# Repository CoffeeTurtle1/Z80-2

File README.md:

# Z802
A Z80 based computer.

The current PCB revision is `Z802-6.kicad_pcb`.

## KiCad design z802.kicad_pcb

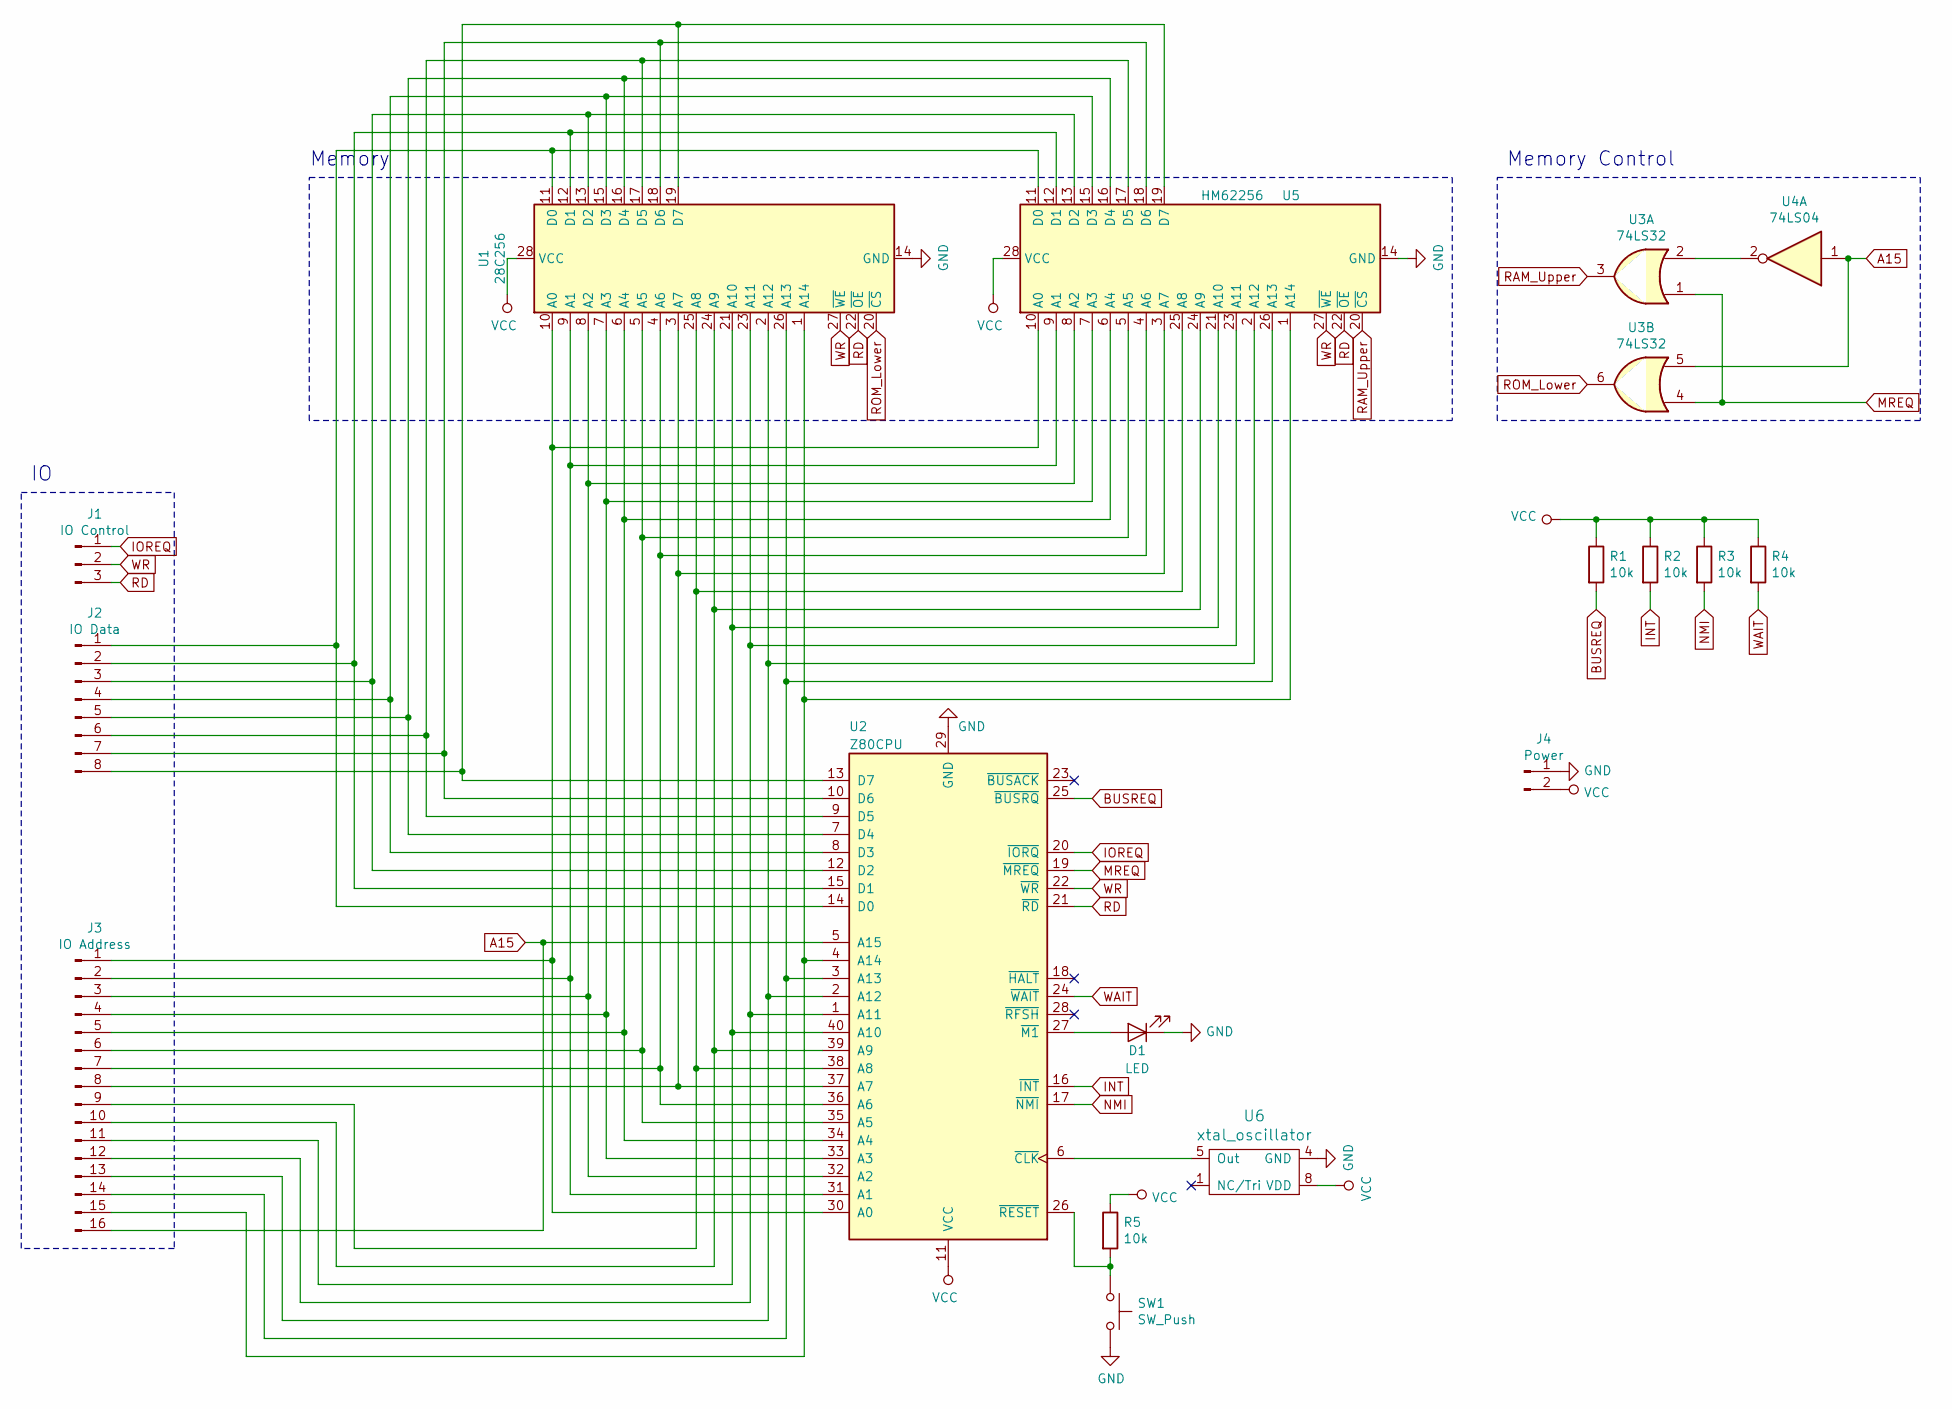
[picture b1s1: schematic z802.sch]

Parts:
D1: LED; LED_D3.0mm
J1: IO Control; PinHeader_1x03_P2.00mm_Vertical
J2: IO Data; PinHeader_1x08_P2.00mm_Vertical
J3: IO Address; PinHeader_1x16_P2.00mm_Vertical
J4: Power; PinHeader_1x02_P2.00mm_Vertical
R1, R2, R3, R4, R5: 10k; R_Axial_DIN0207_L6.3mm_D2.5mm_P7.62mm_Horizontal
SW1: SW_Push; SW_PUSH_6mm
U1: 28C256; DIP-28_W15.24mm
U2: Z80CPU; DIP-40_W15.24mm
U3: 74LS32; DIP-14_W7.62mm
U4: 74LS04; DIP-14_W7.62mm
U5: HM62256; DIP-28_W15.24mm
U6: xtal_oscillator; Oscillator_DIP-8

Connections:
A15: J3.16, U2.5 (A15), U3.5, U4.1
BUSREQ: R1.2, U2.25 (~BUSRQ~)
GND: D1.1 (K), J4.1, SW1.2, U1.14 (GND), U2.29 (GND), U5.14 (GND), U6.4 (GND)
INT: R2.2, U2.16 (~INT~)
IOREQ: J1.1, U2.20 (~IORQ~)
MREQ: U2.19 (~MREQ~), U3.1, U3.4
NMI: R3.2, U2.17 (~NMI~)
unnamed: D1.2 (A), U2.27 (~M1~)
unnamed: J2.1, U1.11 (D0), U2.14 (D0), U5.11 (D0)
unnamed: J2.2, U1.12 (D1), U2.15 (D1), U5.12 (D1)
unnamed: J2.3, U1.13 (D2), U2.12 (D2), U5.13 (D2)
unnamed: J2.4, U1.15 (D3), U2.8 (D3), U5.15 (D3)
unnamed: J2.5, U1.16 (D4), U2.7 (D4), U5.16 (D4)
unnamed: J2.6, U1.17 (D5), U2.9 (D5), U5.17 (D5)
unnamed: J2.7, U1.18 (D6), U2.10 (D6), U5.18 (D6)
unnamed: J2.8, U1.19 (D7), U2.13 (D7), U5.19 (D7)
unnamed: J3.1, U1.10 (A0), U2.30 (A0), U5.10 (A0)
unnamed: J3.2, U1.9 (A1), U2.31 (A1), U5.9 (A1)
unnamed: J3.3, U1.8 (A2), U2.32 (A2), U5.8 (A2)
unnamed: J3.4, U1.7 (A3), U2.33 (A3), U5.7 (A3)
unnamed: J3.5, U1.6 (A4), U2.34 (A4), U5.6 (A4)
unnamed: J3.6, U1.5 (A5), U2.35 (A5), U5.5 (A5)
unnamed: J3.7, U1.4 (A6), U2.36 (A6), U5.4 (A6)
unnamed: J3.8, U1.3 (A7), U2.37 (A7), U5.3 (A7)
unnamed: J3.9, U1.25 (A8), U2.38 (A8), U5.25 (A8)
unnamed: J3.10, U1.24 (A9), U2.39 (A9), U5.24 (A9)
unnamed: J3.11, U1.21 (A10), U2.40 (A10), U5.21 (A10)
unnamed: J3.12, U1.23 (A11), U2.1 (A11), U5.23 (A11)
unnamed: J3.13, U1.2 (A12), U2.2 (A12), U5.2 (A12)
unnamed: J3.14, U1.26 (A13), U2.3 (A13), U5.26 (A13)
unnamed: J3.15, U1.1 (A14), U2.4 (A14), U5.1 (A14)
unnamed: R5.2, SW1.1, U2.26 (~RESET~)
unnamed: U2.6 (~CLK~), U6.5 (Out)
unnamed: U3.2, U4.2
RAM_Upper: U3.3, U5.20 (~CS)
RD: J1.3, U1.22 (~OE), U2.21 (~RD~), U5.22 (~OE)
ROM_Lower: U1.20 (~CS), U3.6
VCC: J4.2, R1.1, R2.1, R3.1, R4.1, R5.1, U1.28 (VCC), U2.11 (VCC), U5.28 (VCC), U6.8 (VDD)
WAIT: R4.2, U2.24 (~WAIT~)
WR: J1.2, U1.27 (~WE), U2.22 (~WR~), U5.27 (~WE)

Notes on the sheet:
Memory Control
Memory

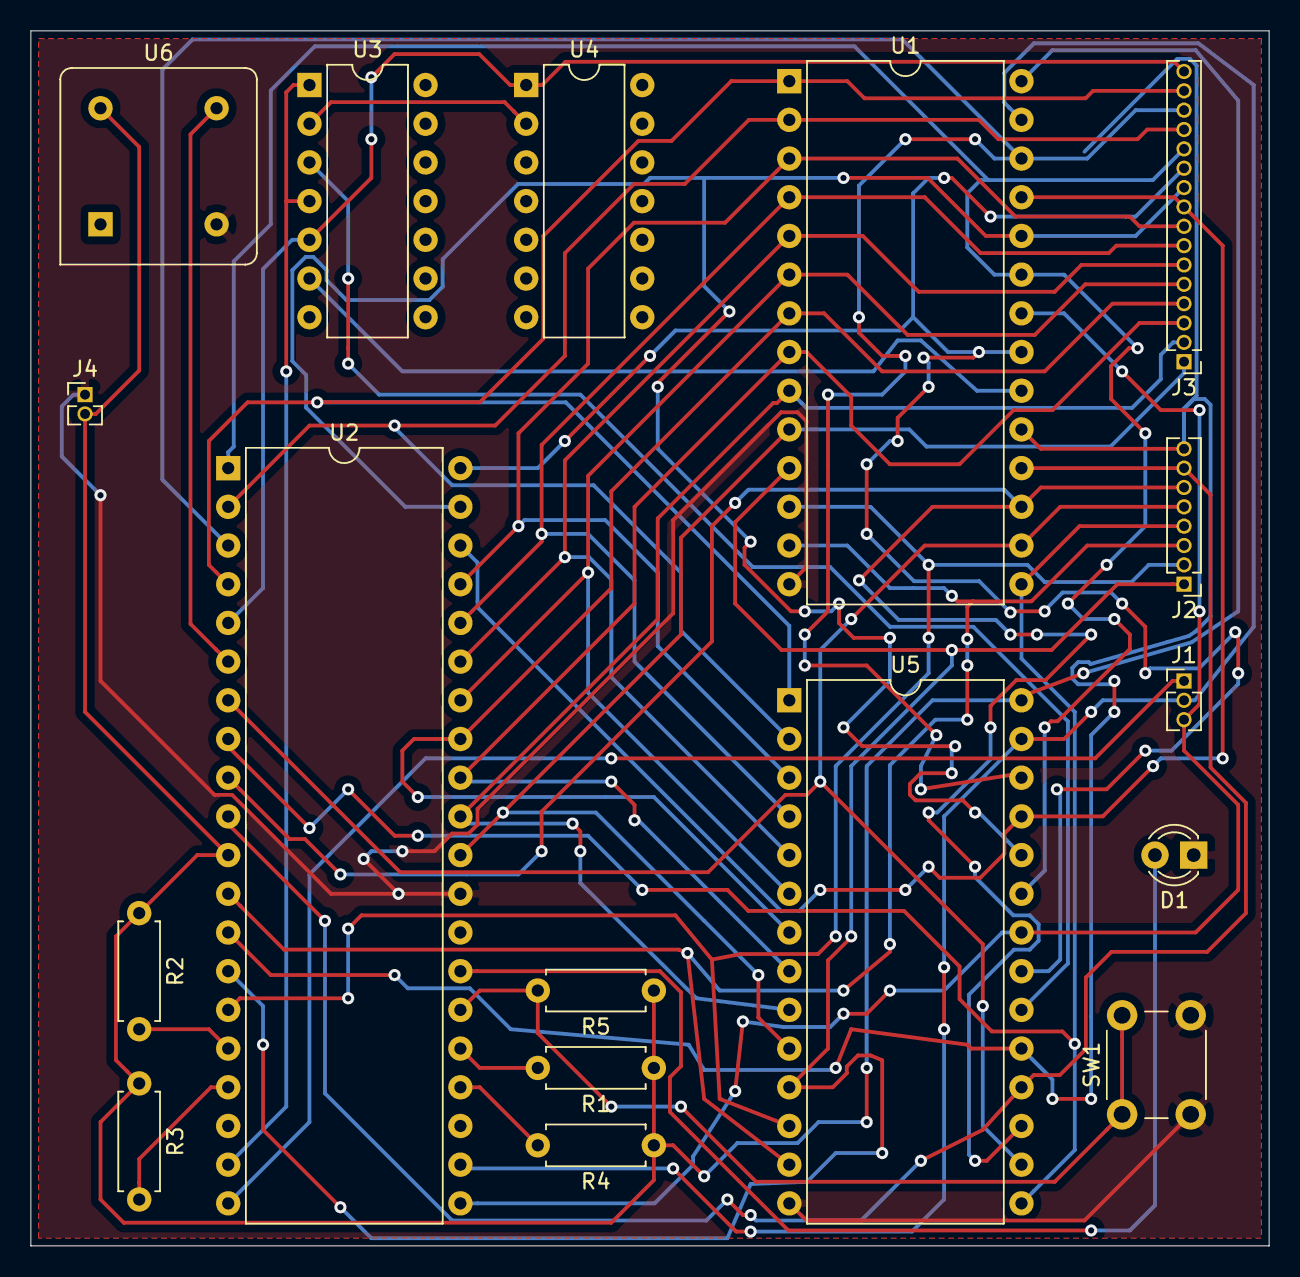
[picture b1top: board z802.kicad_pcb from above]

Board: 2 copper layers, 81.3 x 79.8 mm, 17 parts (0 on the bottom side), 40 nets.

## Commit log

2019-08-25 Initial commit.
2019-08-26 Finish PCB.
2019-09-27 Re-design PCB.
2019-09-28 Re-design PCB for the fourth time.
2019-10-15 Add readme.md.
2019-10-29 Redesign the PCB for the 6th time.
